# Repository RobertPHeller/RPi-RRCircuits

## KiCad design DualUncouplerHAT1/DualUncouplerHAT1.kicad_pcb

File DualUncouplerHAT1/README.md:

# DualUncouplerHAT1

This is the same as DualUncouplerHAT, except it uses GPIO pins 23 and 24 
(BCM 13 and 19, physical pins 33 and 35).

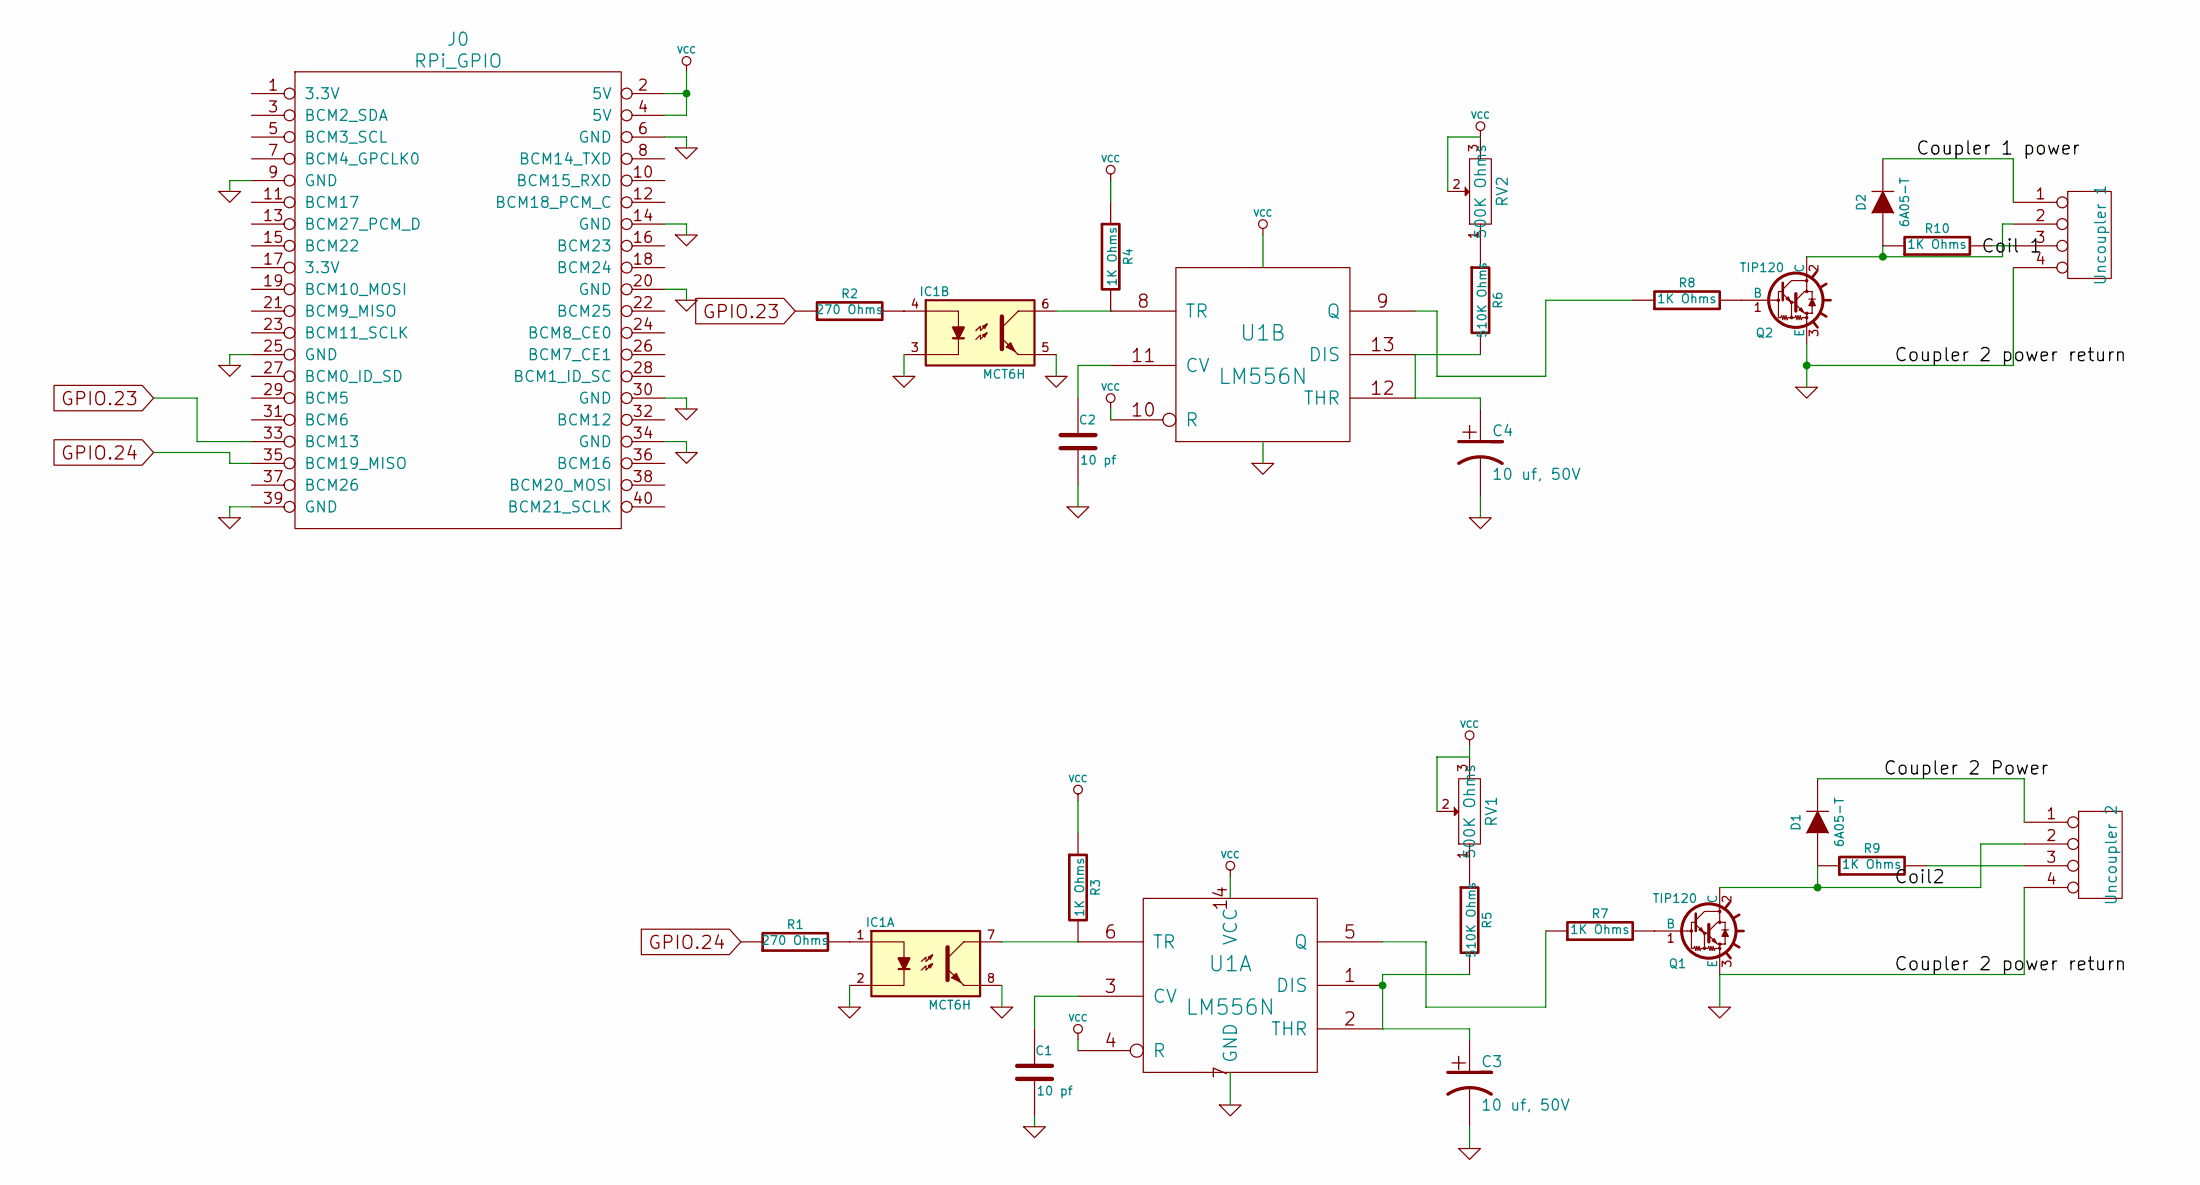
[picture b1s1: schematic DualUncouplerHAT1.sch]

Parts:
C1, C2: 10 pf; Mouser Part Number 594-S100K25SL0N63L6R
C3, C4: 10 uf, 50V; Mouser Part Number 140-REA100M1HBK0511P
D1, D2: 6A05-T; Mouser Part Number 621-6A05-T
IC1: MCT6H; DIP-8__300; Mouser Part Number 782-MCT6H
J0: RPi_GPIO; Pin_Header_Straight_2x20; Mouser Part Number 855-M20-6102045
Q1, Q2: TIP120; TO220; Mouser Part Number 863-TIP120G
R1, R2: 270 Ohms; Mouser Part Number 603-CFR-25JR-52-270R
R3, R4, R7, R8, R9, R10: 1K Ohms; Mouser Part Number 279-2-1623927-3
R5, R6: 510K Ohms; Mouser Part Number 660-CF1/4CT52R514J
RV1, RV2: 500K Ohms; Mouser Part Number 652-3309P-1-504
T1: Uncoupler 1; Mouser Part Number 571-2828374
T2: Uncoupler 2; Mouser Part Number 571-2828374
U1: LM556N; Mouser Part Number 926-LM556CN/NOP

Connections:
/Coil2: D1.1 (A), Q1.2 (C), R9.1, T2.2
/Coil 1: D2.1 (A), Q2.2 (C), R10.1, T1.2
/Coupler 1 power: D2.2 (K), T1.1
/Coupler 2 Power: D1.2 (K), T2.1
GND: C1.2, C2.2, C3.2, C4.2, IC1.2, IC1.3, IC1.5, IC1.8, J0.6 (GND), J0.9 (GND), J0.14 (GND), J0.20 (GND), J0.25 (GND), J0.30 (GND), J0.34 (GND), J0.39 (GND), Q1.3 (E), Q2.3 (E), T1.4, T2.4, U1.7 (GND)
GPIO.23: J0.33 (BCM13), R2.1
GPIO.24: J0.35 (BCM19_MISO), R1.1
unnamed: C1.1, U1.3 (CV)
unnamed: C2.1, U1.11 (CV)
unnamed: IC1.7, R3.2, U1.6 (TR)
unnamed: IC1.6, R4.2, U1.8 (TR)
unnamed: R9.2, T2.3
unnamed: R10.2, T1.3
unnamed: R7.1, U1.5 (Q)
unnamed: C4.1, R6.2, U1.12 (THR), U1.13 (DIS)
unnamed: R8.1, U1.9 (Q)
unnamed: C3.1, R5.2, U1.1 (DIS), U1.2 (THR)
unnamed: Q2.1 (B), R8.2
unnamed: R5.1, RV1.1
unnamed: R6.1, RV2.1
unnamed: Q1.1 (B), R7.2
unnamed: IC1.1, R1.2
unnamed: IC1.4, R2.2
VCC: J0.2 (5V), J0.4 (5V), R3.1, R4.1, RV1.2, RV1.3, RV2.2, RV2.3, U1.4 (R), U1.10 (R), U1.14 (VCC)

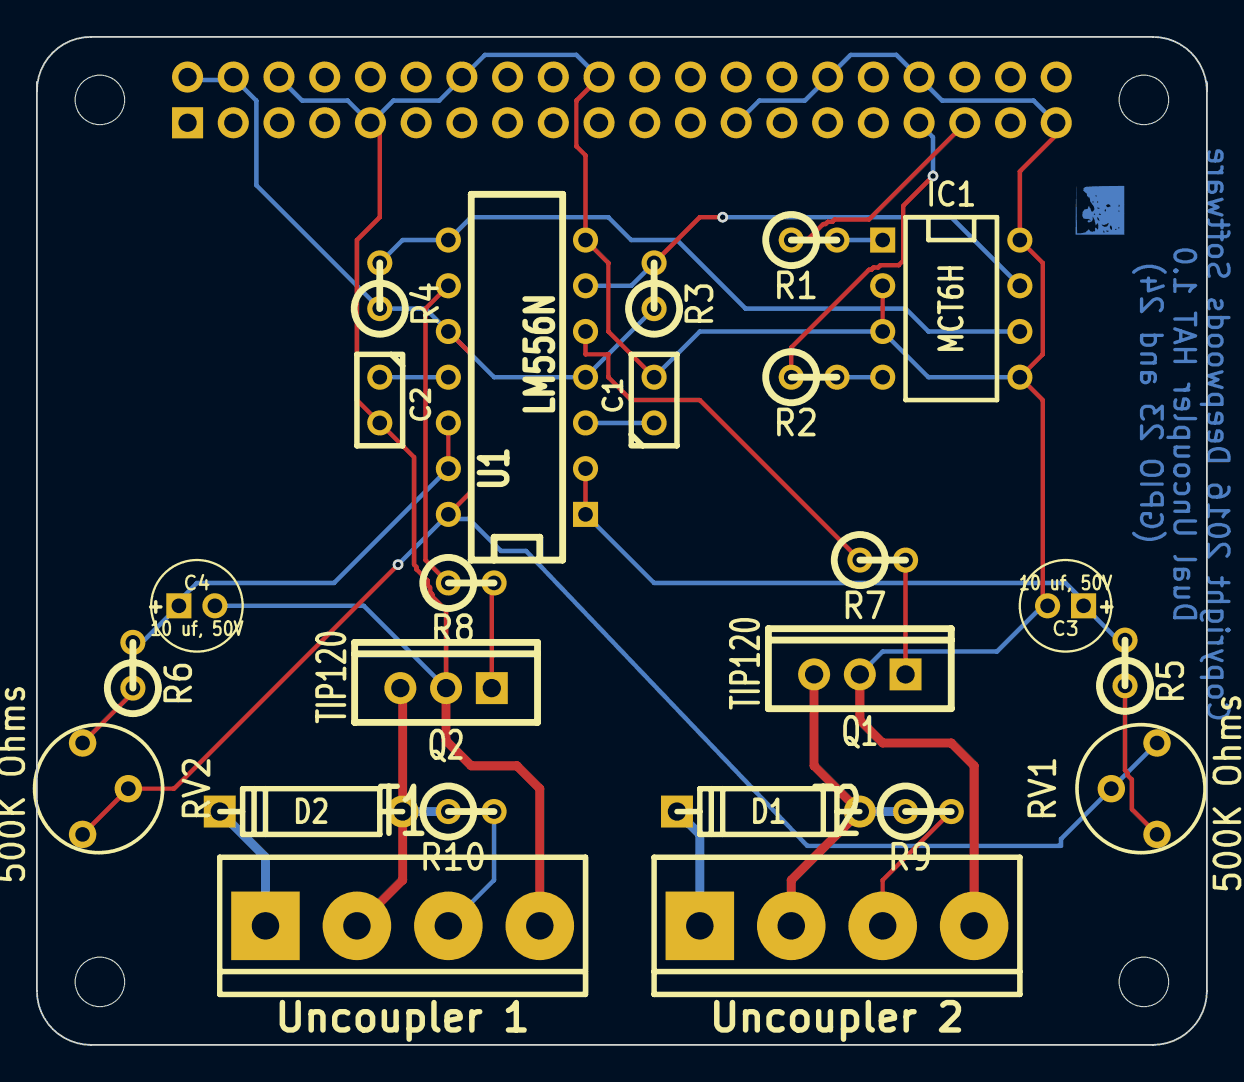
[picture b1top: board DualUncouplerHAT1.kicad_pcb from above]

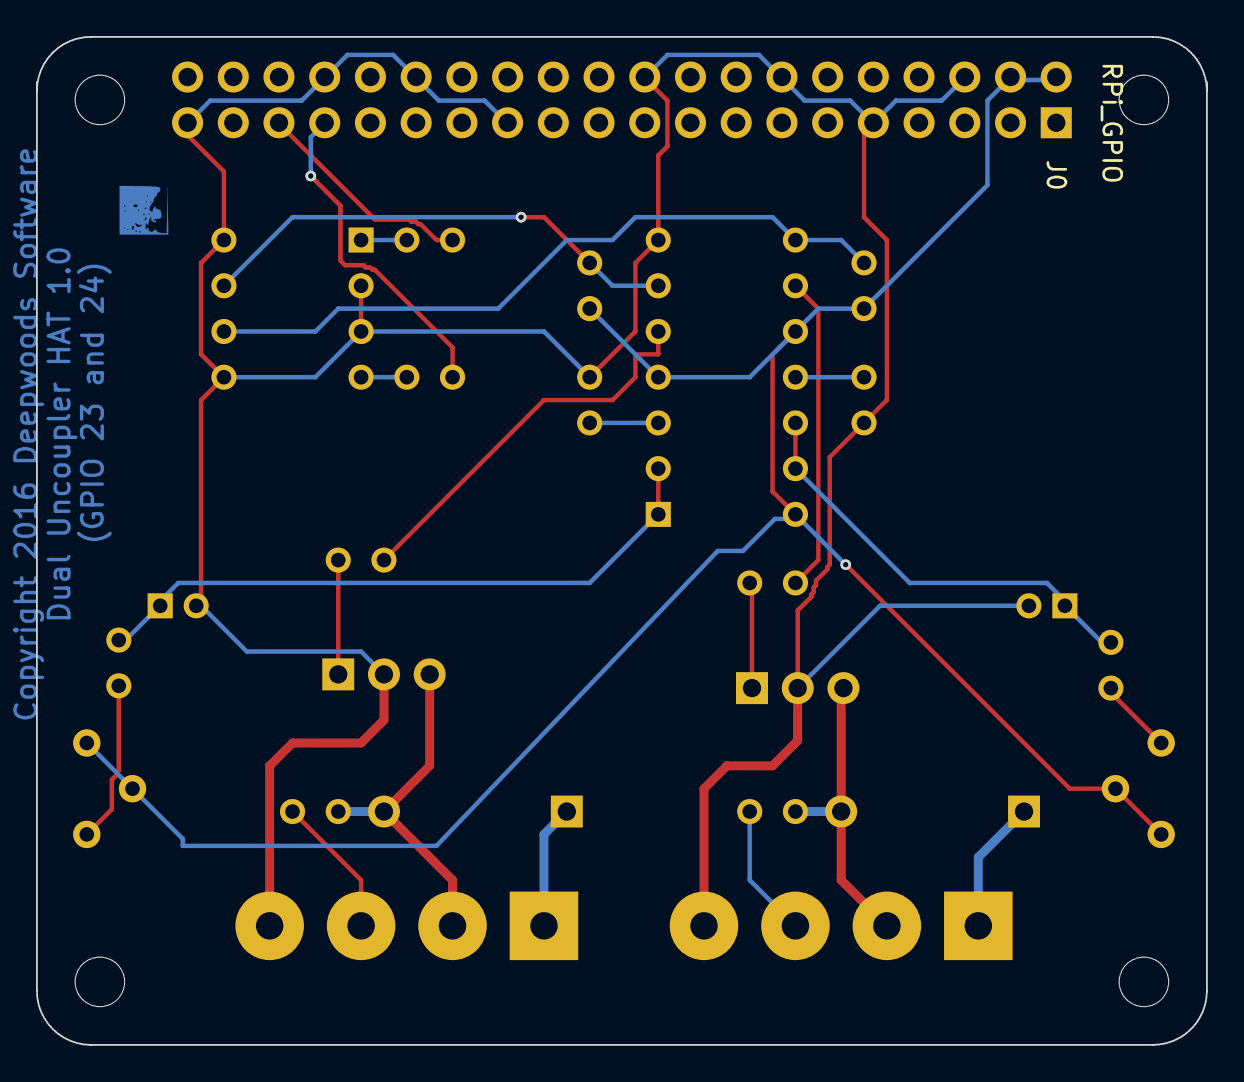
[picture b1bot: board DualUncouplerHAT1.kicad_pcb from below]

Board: 2 copper layers, 65.0 x 56.0 mm, 29 parts (5 on the bottom side), 24 nets.

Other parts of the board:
H1, H2, H3, H4: RPi_Hat_Mounting_Hole

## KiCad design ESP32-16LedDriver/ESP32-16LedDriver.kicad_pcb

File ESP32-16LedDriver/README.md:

# ESP32-16LedDriver

16 on/off LED Driver board using a MCP23017.

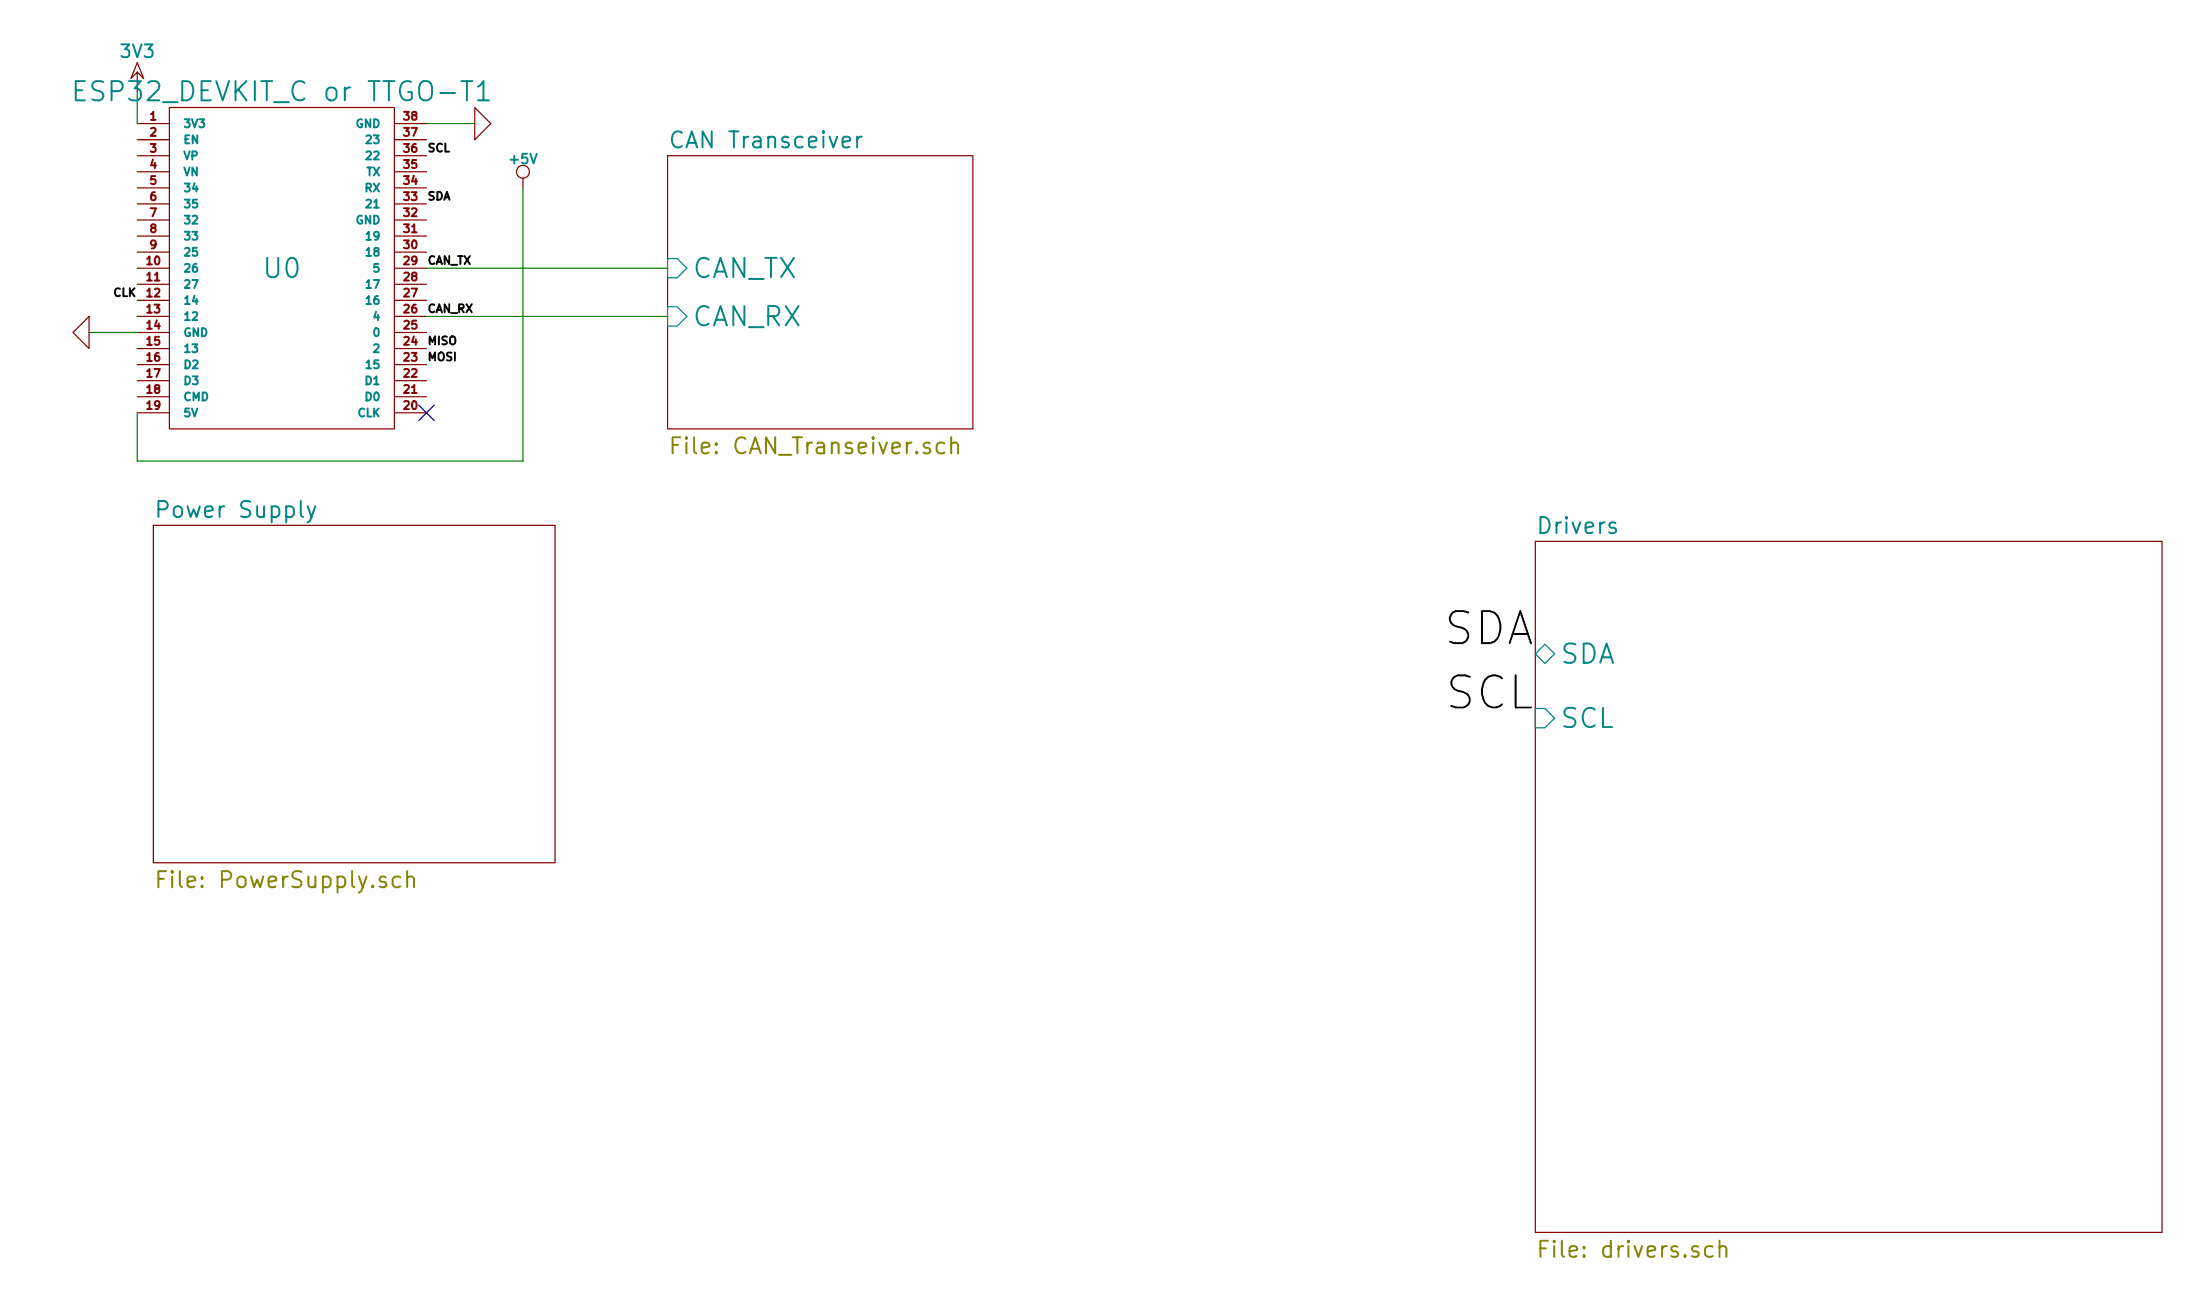
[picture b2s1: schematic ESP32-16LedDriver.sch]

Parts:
U0: ESP32_DEVKIT_C or TTGO-T1

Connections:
3V3: U0.1 (3V3); also elsewhere on the board
+5V: U0.19 (5V); also elsewhere on the board
/CAN Transceiver/CAN_RX: U0.26 (4); also elsewhere on the board
/CAN Transceiver/CAN_TX: U0.29 (5); also elsewhere on the board
/Drivers/SCL: U0.36 (22); also elsewhere on the board
/Drivers/SDA: U0.33 (21); also elsewhere on the board
GND: U0.14 (GND), U0.38 (GND); also elsewhere on the board

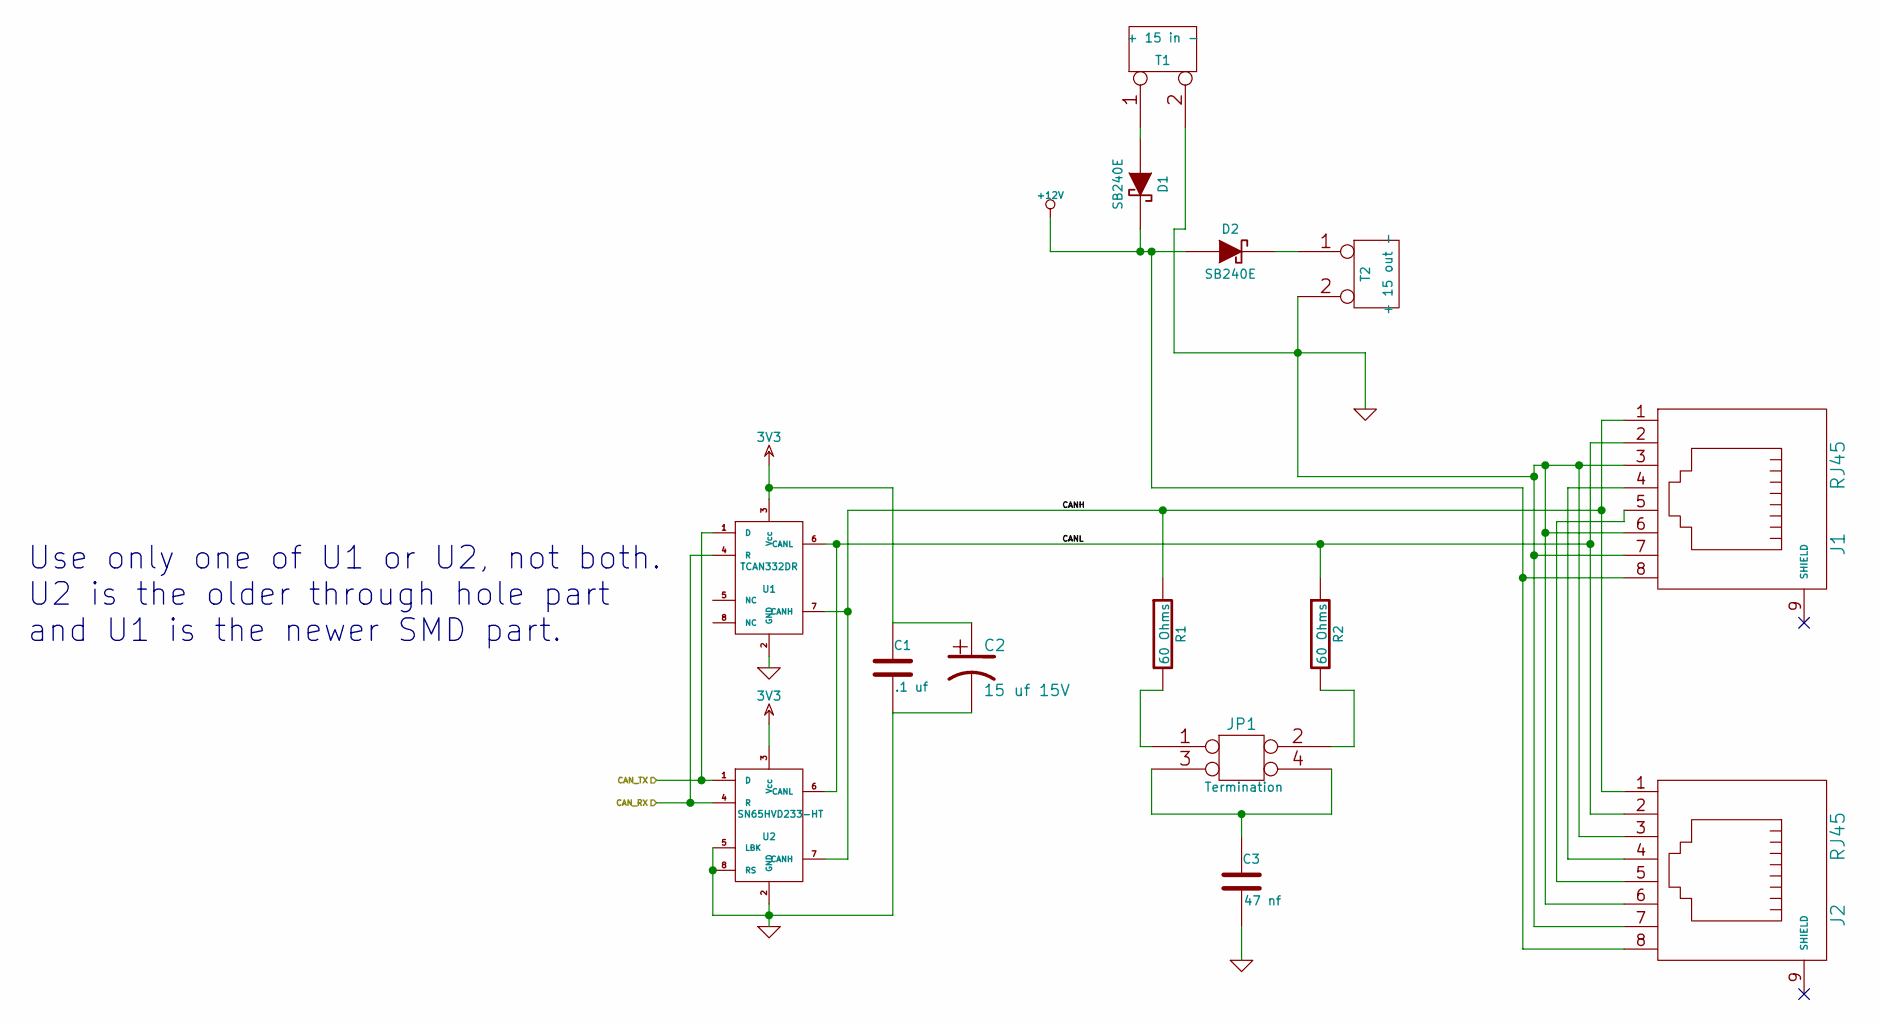
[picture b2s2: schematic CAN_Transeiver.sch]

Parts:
C1: .1 uf
C2: 15 uf 15V
C3: 47 nf
D1, D2: SB240E
J1, J2: RJ45
JP1: Termination
R1, R2: 60 Ohms
T1: + 15 in -
T2: + 15 out -
U1: TCAN332DR
U2: SN65HVD233-HT

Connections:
3V3: C1.1, C2.1, U1.3 (Vcc), U2.3 (Vcc); also elsewhere on the board
+12V: D1.2 (K), D2.1 (A), J1.8, J2.8; also elsewhere on the board
/CAN Transceiver/CANH: J1.1, J2.1, R1.1, U1.7 (CANH), U2.7 (CANH)
/CAN Transceiver/CANL: J1.2, J2.2, R2.1, U1.6 (CANL), U2.6 (CANL)
/CAN Transceiver/CAN_RX: U1.4 (R), U2.4 (R); also elsewhere on the board
/CAN Transceiver/CAN_TX: U1.1 (D), U2.1 (D); also elsewhere on the board
GND: C1.2, C2.2, C3.2, J1.3, J1.6, J1.7, J2.3, J2.6, J2.7, T1.2 (PM), T2.2 (PM), U1.2 (GND), U2.2 (GND), U2.5 (LBK), U2.8 (RS); also elsewhere on the board
unnamed: JP1.2, R2.2
unnamed: C3.1, JP1.3, JP1.4
unnamed: JP1.1, R1.2
unnamed: J1.5, J2.5
unnamed: D2.2 (K), T2.1
unnamed: D1.1 (A), T1.1
unnamed: J1.4, J2.4

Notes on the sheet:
Use only one of U1 or U2, not both. U2 is the older through hole part and U1 is the newer SMD part.

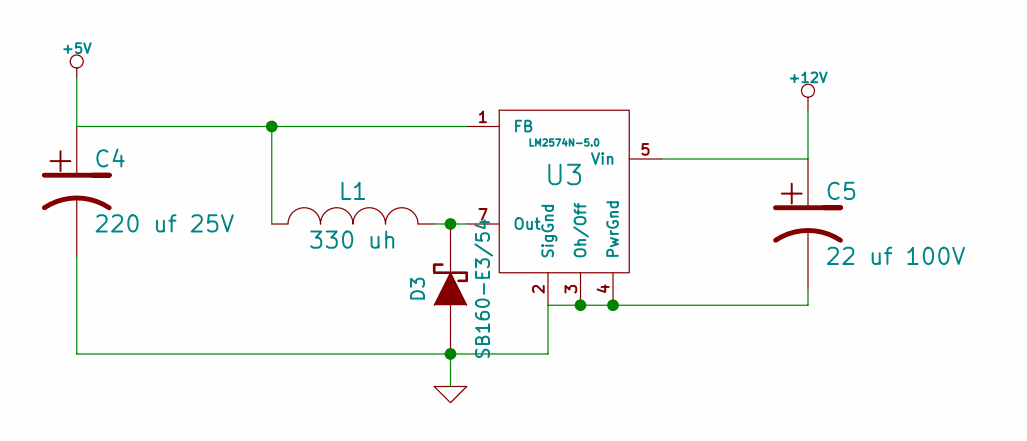
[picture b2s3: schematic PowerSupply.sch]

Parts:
C4: 220 uf 25V
C5: 22 uf 100V
D3: SB160-E3/54
L1: 330 uh
U3: LM2574N-5.0

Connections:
+5V: C4.1, L1.1, U3.1 (FB); also elsewhere on the board
+12V: C5.1, U3.5 (Vin); also elsewhere on the board
GND: C4.2, C5.2, D3.1 (A), U3.2 (SigGnd), U3.3 (Oh/Off), U3.4 (PwrGnd); also elsewhere on the board
unnamed: D3.2 (K), L1.2, U3.7 (Out)

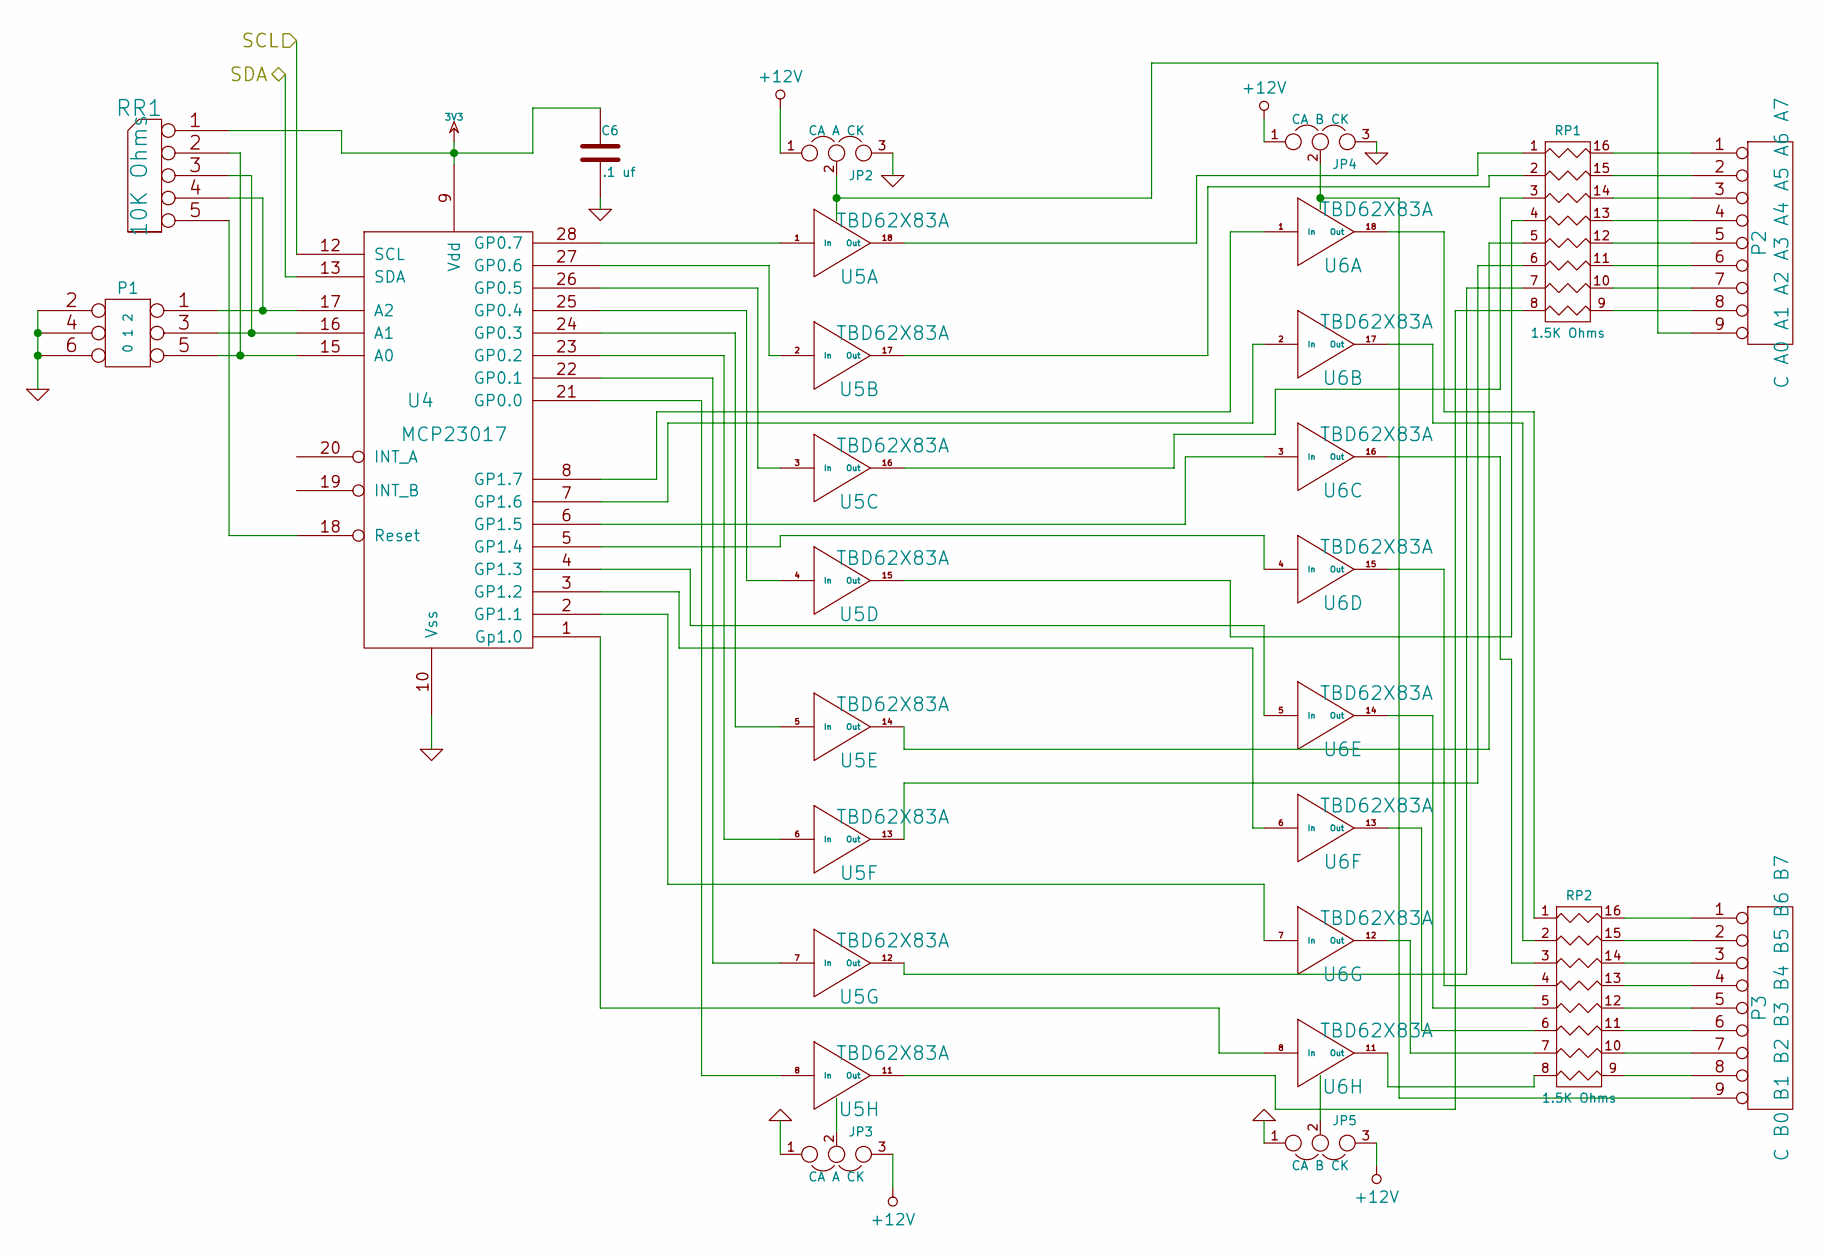
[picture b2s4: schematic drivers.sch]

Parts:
C6: .1 uf
JP2, JP3: CA A CK
JP4, JP5: CA B CK
P1: 0 1 2
P2: C A0 A1 A2 A3 A4 A5 A6 A7
P3: C B0 B1 B2 B3 B4 B5 B6 B7
RP1, RP2: 1.5K Ohms
RR1: 10K Ohms
U4: MCP23017
U5, U6: TBD62X83A

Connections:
3V3: C6.1, RR1.1 (COM), U4.9 (Vdd); also elsewhere on the board
+12V: JP2.1, JP3.3, JP4.1, JP5.3; also elsewhere on the board
/Drivers/SCL: U4.12 (SCL); also elsewhere on the board
/Drivers/SDA: U4.13 (SDA); also elsewhere on the board
GND: C6.2, JP2.3, JP3.1, JP4.3, JP5.1, P1.2, P1.4, P1.6, U4.10 (Vss); also elsewhere on the board
unnamed: U4.7 (GP1.6), U6.2 (In)
unnamed: U4.6 (GP1.5), U6.3 (In)
unnamed: U4.5 (GP1.4), U6.4 (In)
unnamed: U4.4 (GP1.3), U6.5 (In)
unnamed: U4.22 (GP0.1), U5.7 (In)
unnamed: U4.25 (GP0.4), U5.4 (In)
unnamed: U4.24 (GP0.3), U5.5 (In)
unnamed: U4.23 (GP0.2), U5.6 (In)
unnamed: U4.21 (GP0.0), U5.8 (In)
unnamed: U4.8 (GP1.7), U6.1 (In)
unnamed: RP1.2, U5.17 (Out)
unnamed: RP1.3, U5.16 (Out)
unnamed: RP1.4, U5.15 (Out)
unnamed: RP1.5, U5.14 (Out)
unnamed: U4.1 (Gp1.0), U6.8 (In)
unnamed: U4.3 (GP1.2), U6.6 (In)
unnamed: U4.2 (GP1.1), U6.7 (In)
unnamed: RP1.1, U5.18 (Out)
unnamed: RP1.7, U5.12 (Out)
unnamed: RP2.1, U6.18 (Out)
unnamed: RP2.3, U6.16 (Out)
unnamed: JP3.2, U5.9 (IC)
unnamed: JP5.2, U6.9 (IC)
unnamed: P2.8, RP1.9 (R8)
unnamed: P2.7, RP1.10 (R7)
unnamed: U4.28 (GP0.7), U5.1 (In)
unnamed: U4.27 (GP0.6), U5.2 (In)
unnamed: U4.26 (GP0.5), U5.3 (In)
unnamed: P3.3, RP2.14 (R3)
unnamed: RP2.7, U6.12 (Out)
unnamed: RP2.8, U6.11 (Out)
unnamed: P3.8, RP2.9 (R8)
unnamed: P3.7, RP2.10 (R7)
unnamed: P3.6, RP2.11 (R6)
unnamed: P3.5, RP2.12 (R5)
unnamed: P3.4, RP2.13 (R4)
unnamed: P3.2, RP2.15 (R2)
unnamed: P3.1, RP2.16 (R1)
unnamed: P2.1, RP1.16 (R1)
unnamed: P2.2, RP1.15 (R2)
unnamed: P2.3, RP1.14 (R3)
unnamed: P2.4, RP1.13 (R4)
unnamed: P2.5, RP1.12 (R5)
unnamed: P2.6, RP1.11 (R6)
unnamed: P1.5, RR1.2, U4.15 (A0)
unnamed: P1.3, RR1.3, U4.16 (A1)
unnamed: P1.1, RR1.4, U4.17 (A2)
unnamed: RR1.5, U4.18 (Reset)
unnamed: JP4.2, P3.9, U6.10 (OC)
unnamed: JP2.2, P2.9, U5.10 (OC)
unnamed: RP1.8, U5.11 (Out)
unnamed: RP2.2, U6.17 (Out)
unnamed: RP1.6, U5.13 (Out)
unnamed: RP2.5, U6.14 (Out)
unnamed: RP2.4, U6.15 (Out)
unnamed: RP2.6, U6.13 (Out)

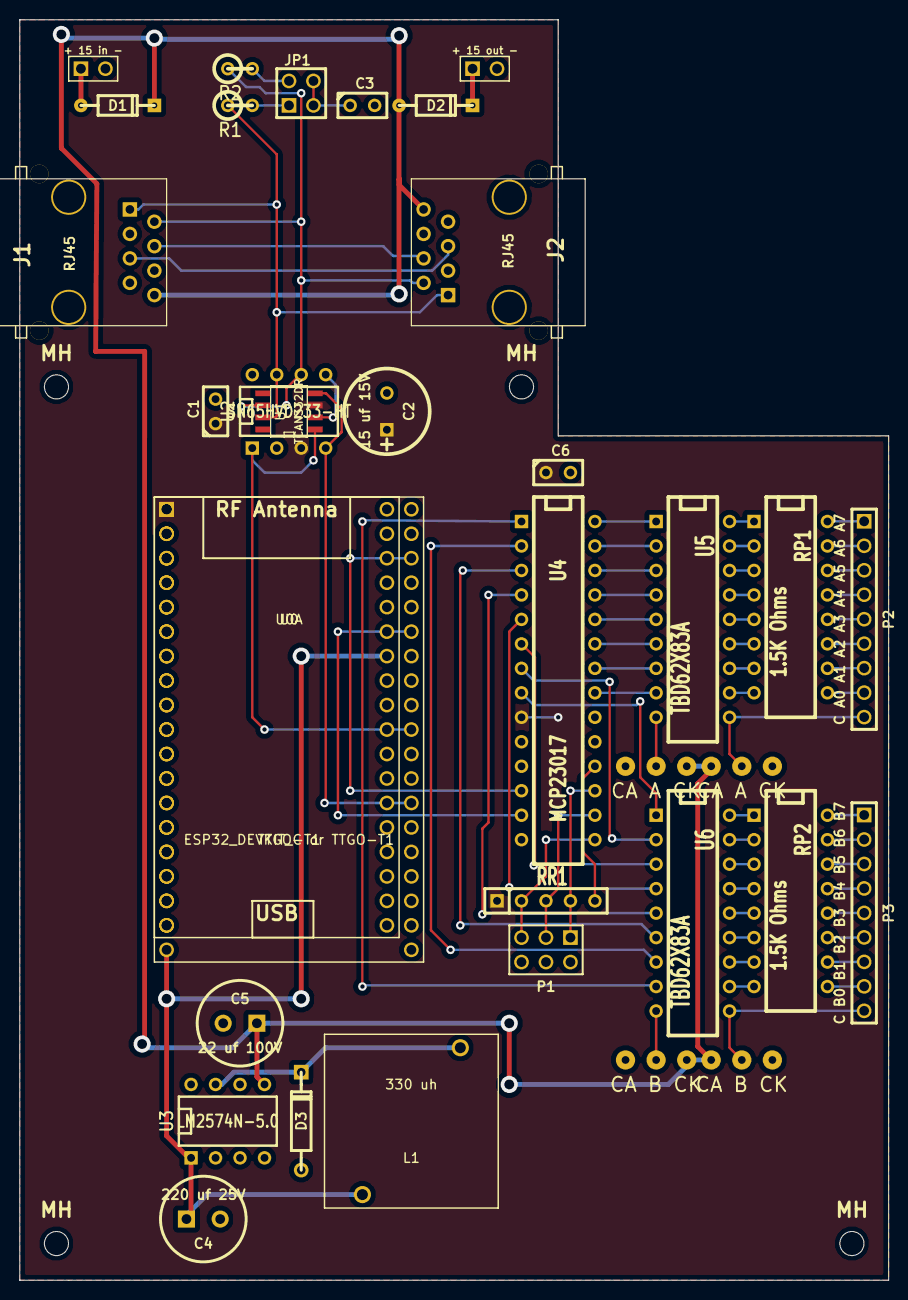
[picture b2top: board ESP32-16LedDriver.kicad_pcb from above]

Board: 2 copper layers, 90.2 x 130.8 mm, 39 parts (0 on the bottom side), 74 nets.

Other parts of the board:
MH: MountingHole_2-5mm_RevA_Date21Jun2010
MH#2, MH#3, MH#4: MountingHole_2-5mm_RevA_Date21Jun2010
U0A: TTGO-T1; TIGO-T1

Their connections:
3V3: U0A.1; also elsewhere on the board
+5V: U0A.30; also elsewhere on the board
/CAN Transceiver/CAN_RX: U0A.24; also elsewhere on the board
/CAN Transceiver/CAN_TX: U0A.27; also elsewhere on the board
/Drivers/SCL: U0A.34; also elsewhere on the board
/Drivers/SDA: U0A.31; also elsewhere on the board
GND: U0A.14, U0A.36; also elsewhere on the board

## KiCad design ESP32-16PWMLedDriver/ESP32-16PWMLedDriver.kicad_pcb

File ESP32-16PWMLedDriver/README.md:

# ESP32-16PWMLedDriver

16 LED PWM driver board using a PCA9685.

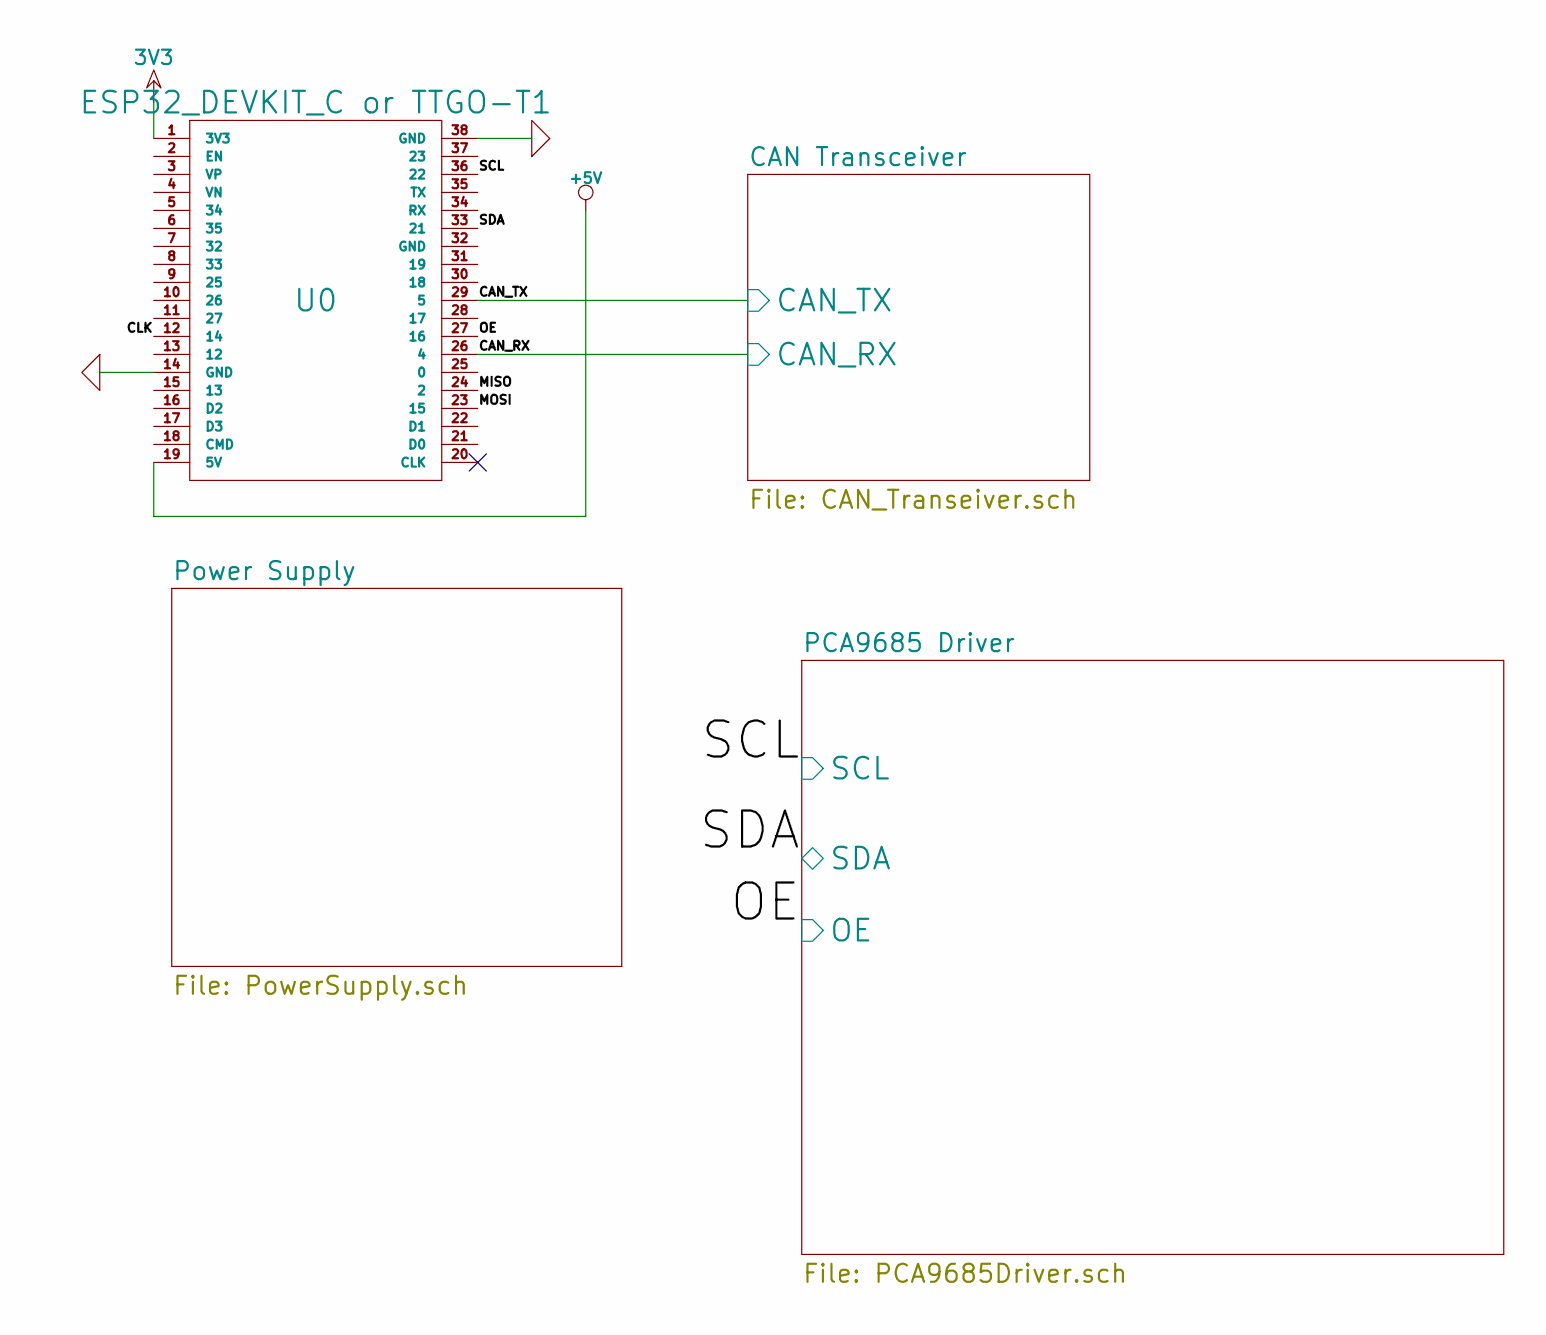
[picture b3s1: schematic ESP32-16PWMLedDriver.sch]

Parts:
U0: ESP32_DEVKIT_C or TTGO-T1

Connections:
3V3: U0.1 (3V3); also elsewhere on the board
+5V: U0.19 (5V); also elsewhere on the board
/CAN Transceiver/CAN_RX: U0.26 (4); also elsewhere on the board
/CAN Transceiver/CAN_TX: U0.29 (5); also elsewhere on the board
/PCA9685 Driver/OE: U0.27 (16); also elsewhere on the board
/PCA9685 Driver/SCL: U0.36 (22); also elsewhere on the board
/PCA9685 Driver/SDA: U0.33 (21); also elsewhere on the board
GND: U0.14 (GND), U0.38 (GND); also elsewhere on the board

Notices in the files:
DualUncouplerHAT1/DualUncouplerHAT1.kicad_pcb:
Copyright 2016 Deepwoods Software
ESP32-D0WD-V3-MultiFunction/ESP32-D0WD-V3-MultiFunction.kicad_pcb:
(c) Copyright 2022 Deepwoods Software
ESP32-MultiFunction/ESP32-MultiFunction.kicad_pcb:
(C) 2021 Deepwoods Software
